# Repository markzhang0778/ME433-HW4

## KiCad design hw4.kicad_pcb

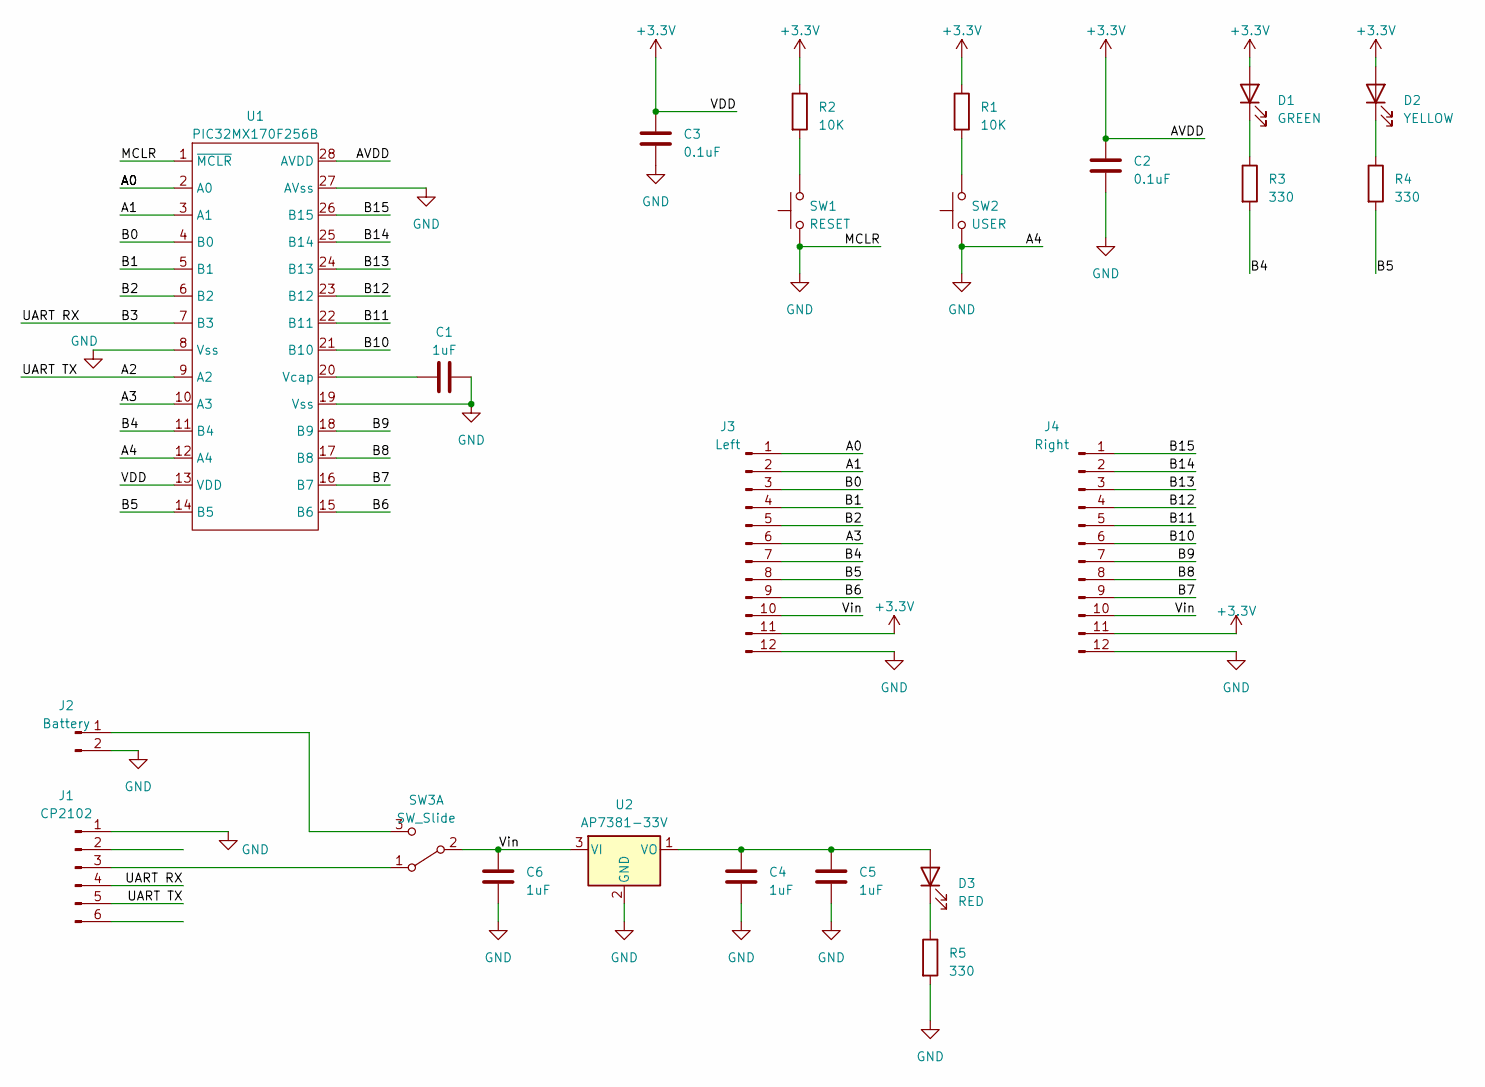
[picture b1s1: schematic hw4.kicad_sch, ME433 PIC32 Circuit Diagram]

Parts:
C1, C4, C5, C6: 1uF; C_Disc_D5.1mm_W3.2mm_P5.00mm
C2, C3: 0.1uF; C_Disc_D3.4mm_W2.1mm_P2.50mm
D1: GREEN; LED_D3.0mm
D2: YELLOW; LED_D3.0mm
D3: RED; LED_D3.0mm
J1: CP2102; PinSocket_1x06_P2.54mm_Vertical
J2: Battery; PinSocket_1x02_P2.54mm_Vertical
J3: Left; PinSocket_1x12_P2.54mm_Vertical
J4: Right; PinSocket_1x12_P2.54mm_Vertical
R1, R2: 10K; R_Axial_DIN0207_L6.3mm_D2.5mm_P7.62mm_Horizontal
R3, R4, R5: 330; R_Axial_DIN0207_L6.3mm_D2.5mm_P7.62mm_Horizontal
SW1: RESET; Pushbutton_sw
SW2: USER; Pushbutton_sw
SW3: SW_Slide; Slide_sw
U1: PIC32MX170F256B; DIP-28_W7.62mm_Socket
U2: AP7381-33V; TO-92L_Inline

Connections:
+3.3V: C2.1, C3.2, D1.2 (A), D2.2 (A), J3.11, J4.11, R1.1, R2.1, U1.13 (VDD), U1.28 (AVDD)
/A0: J3.1, U1.2 (A0)
/A1: J3.2, U1.3 (A1)
/A2: J1.5, U1.9 (A2)
/A3: J3.6, U1.10 (A3)
/B0: J3.3, U1.4 (B0)
/B1: J3.4, U1.5 (B1)
/B2: J3.5, U1.6 (B2)
/B3: J1.4, U1.7 (B3)
/B4: J3.7, R3.2, U1.11 (B4)
/B5: J3.8, R4.2, U1.14 (B5)
/B6: J3.9, U1.15 (B6)
/B7: J4.9, U1.16 (B7)
/B8: J4.8, U1.17 (B8)
/B9: J4.7, U1.18 (B9)
/B10: J4.6, U1.21 (B10)
/B11: J4.5, U1.22 (B11)
/B12: J4.4, U1.23 (B12)
/B13: J4.3, U1.24 (B13)
/B14: J4.2, U1.25 (B14)
/B15: J4.1, U1.26 (B15)
/Vin: C6.1, J3.10, J4.10, SW3.2 (B), U2.3 (VI)
GND: C1.1, C2.2, C3.1, C4.2, C5.2, C6.2, J1.1, J2.2, J3.12, J4.12, R5.2, SW1.2, SW2.2, U1.1 (~MCLR), U1.8 (Vss), U1.12 (A4), U1.19 (Vss), U1.27 (AVss), U2.2 (GND)
unnamed: D1.1 (K), R3.1
unnamed: D2.1 (K), R4.1
unnamed: C4.1, C5.1, D3.2 (A), U2.1 (VO)
unnamed: D3.1 (K), R5.1
unnamed: J1.3, SW3.1 (A)
unnamed: J2.1, SW3.3 (C)
unnamed: R1.2, SW2.1
unnamed: R2.2, SW1.1
unnamed: C1.2, U1.20 (Vcap)

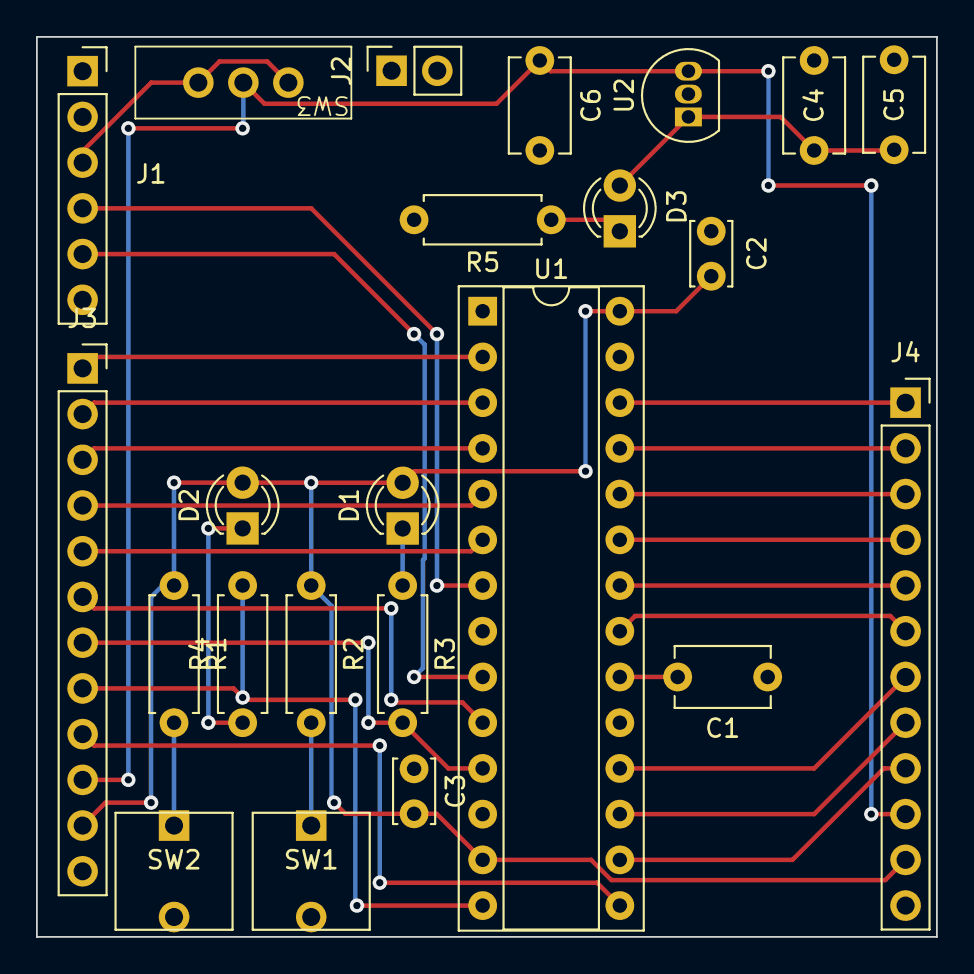
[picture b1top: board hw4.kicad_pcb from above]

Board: 2 copper layers, 50.0 x 50.0 mm, 23 parts (0 on the bottom side), 31 nets.
